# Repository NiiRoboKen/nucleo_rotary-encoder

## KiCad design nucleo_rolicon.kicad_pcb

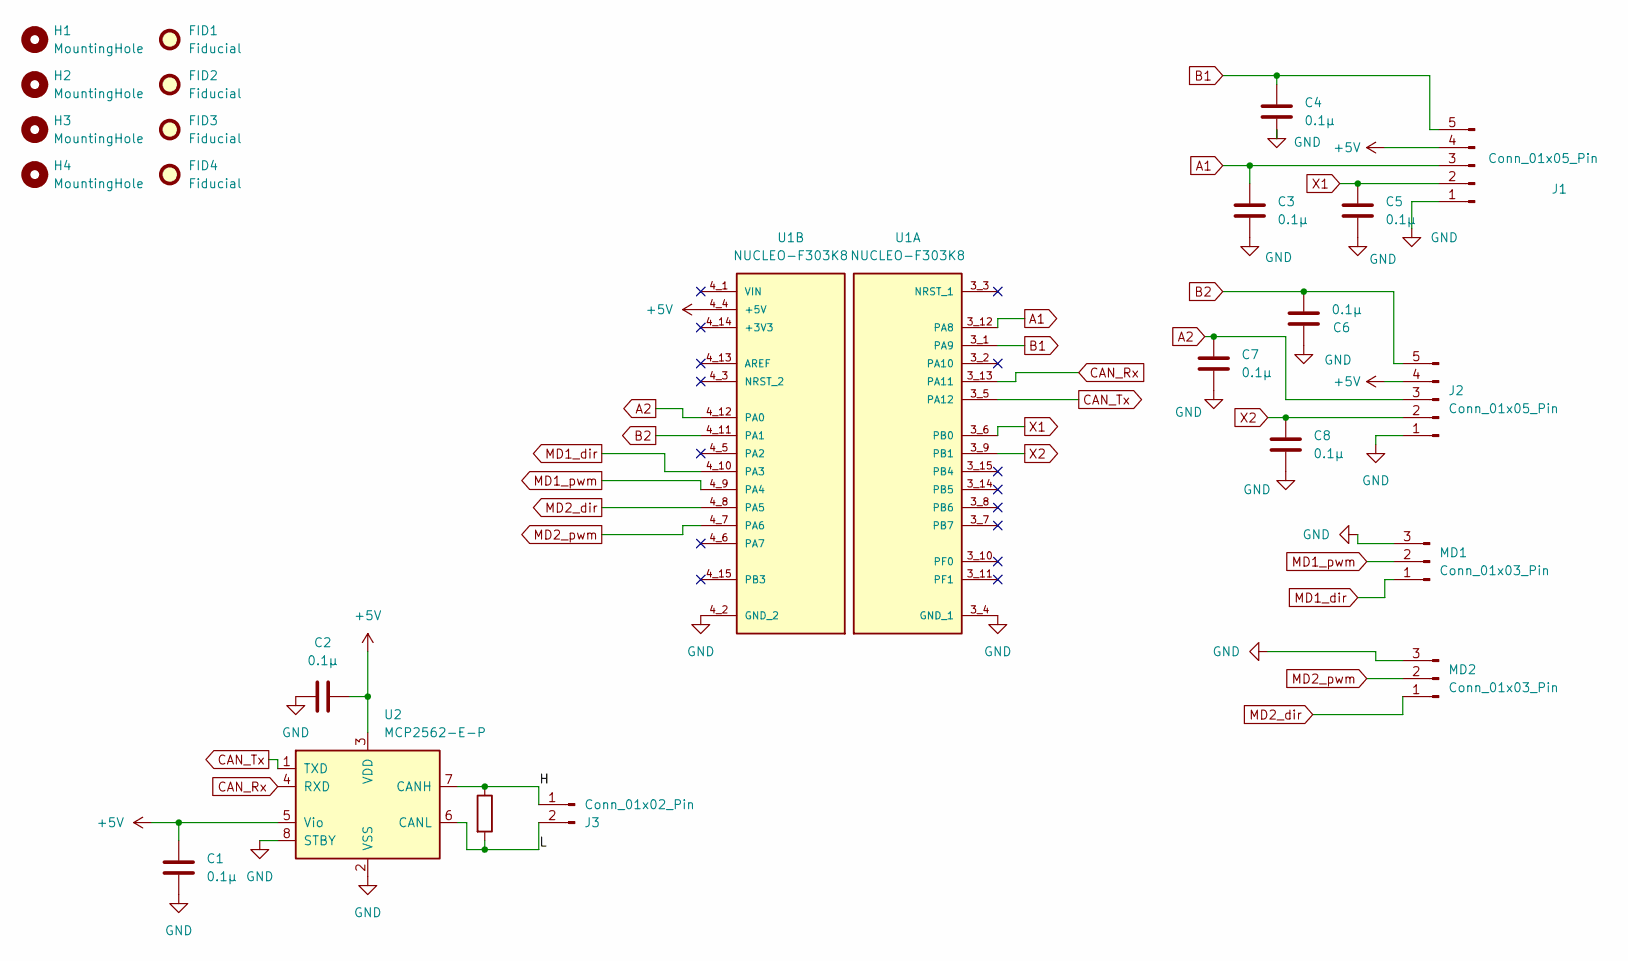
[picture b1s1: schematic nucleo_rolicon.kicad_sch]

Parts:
C1, C2, C3, C4, C5, C6, C7, C8: 0.1μ; C_Disc_D3.0mm_W2.0mm_P2.50mm
FID1, FID2, FID3, FID4: Fiducial; Fiducial_0.5mm_Mask1.5mm
H1, H2, H3, H4: MountingHole; MountingHole_2.1mm
J1, J2: Conn_01x05_Pin; JST_XA_S05B-XASK-1N-BN_1x05_P2.50mm_Horizontal
J3: Conn_01x02_Pin; JST_XH_B2B-XH-A_1x02_P2.50mm_Vertical
MD1, MD2: Conn_01x03_Pin; JST_XA_S03B-XASK-1N-BN_1x03_P2.50mm_Horizontal
R1: 120; R_Axial_DIN0207_L6.3mm_D2.5mm_P10.16mm_Horizontal
U1: NUCLEO-F303K8; MODULE_NUCLEO-F303K8; PARTREV 5
U2: MCP2562-E-P; DIP-8_W7.62mm

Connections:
+5V: C1.2, C2.2, J1.4, J2.4, U1.4_4 (+5V), U2.3 (VDD), U2.5 (Vio)
/H: J3.1, R1.1, U2.7 (CANH)
/L: J3.2, R1.2, U2.6 (CANL)
A1: C3.1, J1.3, U1.3_12 (PA8)
A2: C7.1, J2.3, U1.4_12 (PA0)
B1: C4.1, J1.5, U1.3_1 (PA9)
B2: C6.2, J2.5, U1.4_11 (PA1)
CAN_Rx: U1.3_13 (PA11), U2.4 (RXD)
CAN_Tx: U1.3_5 (PA12), U2.1 (TXD)
GND: C1.1, C2.1, C3.2, C4.2, C5.2, C6.1, C7.2, C8.2, J1.1, J2.1, MD1.3, MD2.3, U1.3_4 (GND_1), U1.4_2 (GND_2), U2.2 (VSS), U2.8 (STBY)
MD1_dir: MD1.1, U1.4_10 (PA3)
MD1_pwm: MD1.2, U1.4_9 (PA4)
MD2_dir: MD2.1, U1.4_8 (PA5)
MD2_pwm: MD2.2, U1.4_7 (PA6)
X1: C5.1, J1.2, U1.3_6 (PB0)
X2: C8.1, J2.2, U1.3_9 (PB1)

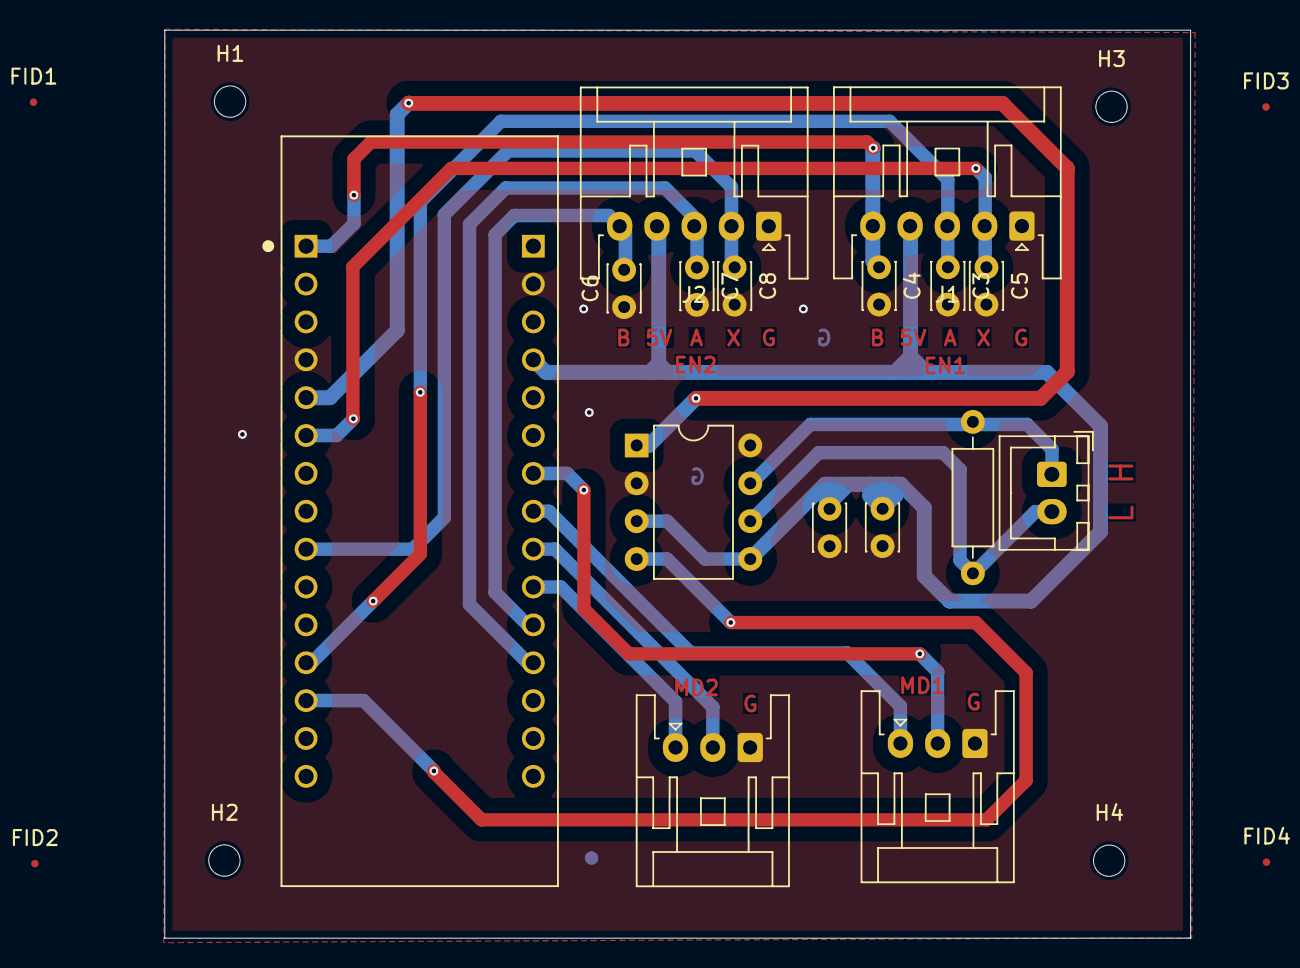
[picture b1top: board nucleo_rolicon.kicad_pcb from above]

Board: 2 copper layers, 68.8 x 60.9 mm, 24 parts (0 on the bottom side), 16 nets.

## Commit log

2024-07-16 Feat:ノイズ抑制トランジスタを追加
